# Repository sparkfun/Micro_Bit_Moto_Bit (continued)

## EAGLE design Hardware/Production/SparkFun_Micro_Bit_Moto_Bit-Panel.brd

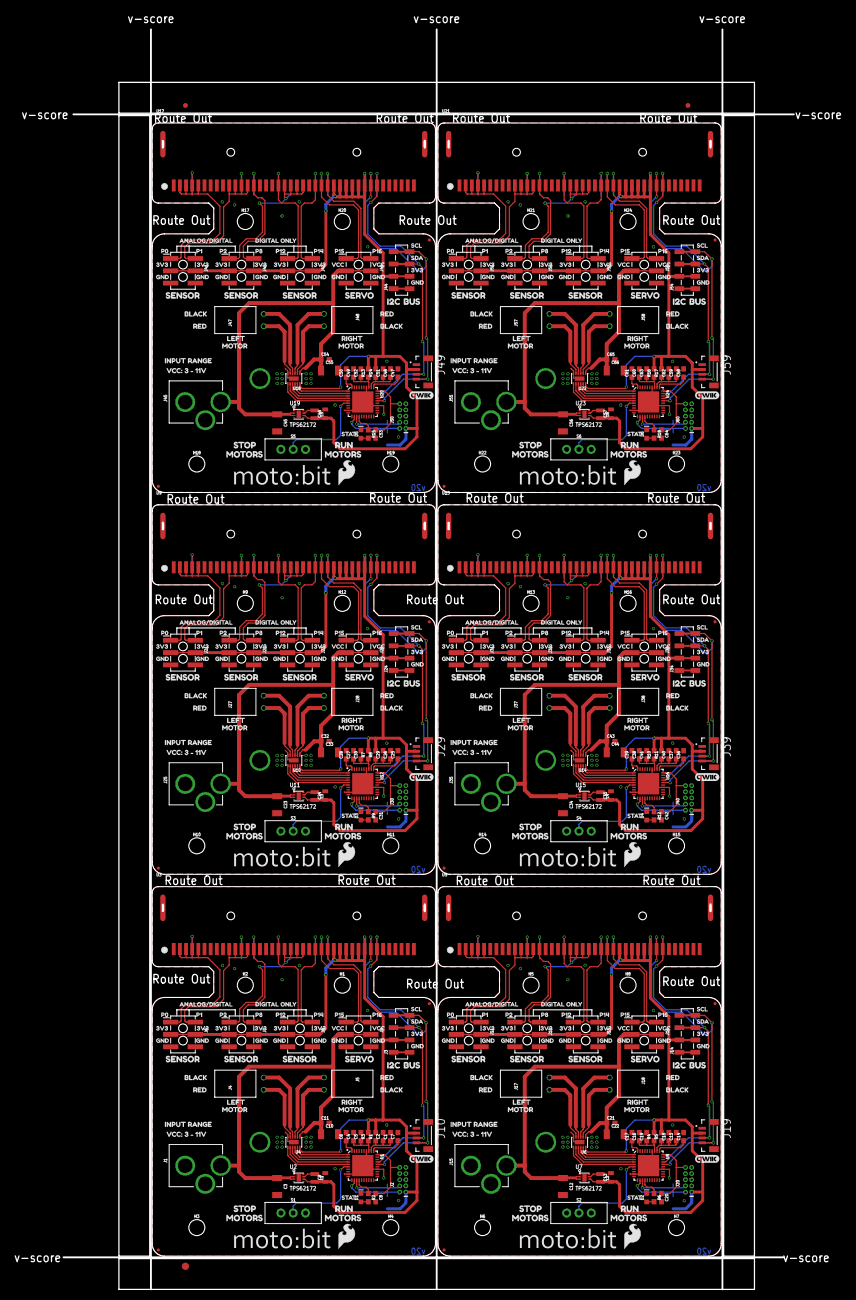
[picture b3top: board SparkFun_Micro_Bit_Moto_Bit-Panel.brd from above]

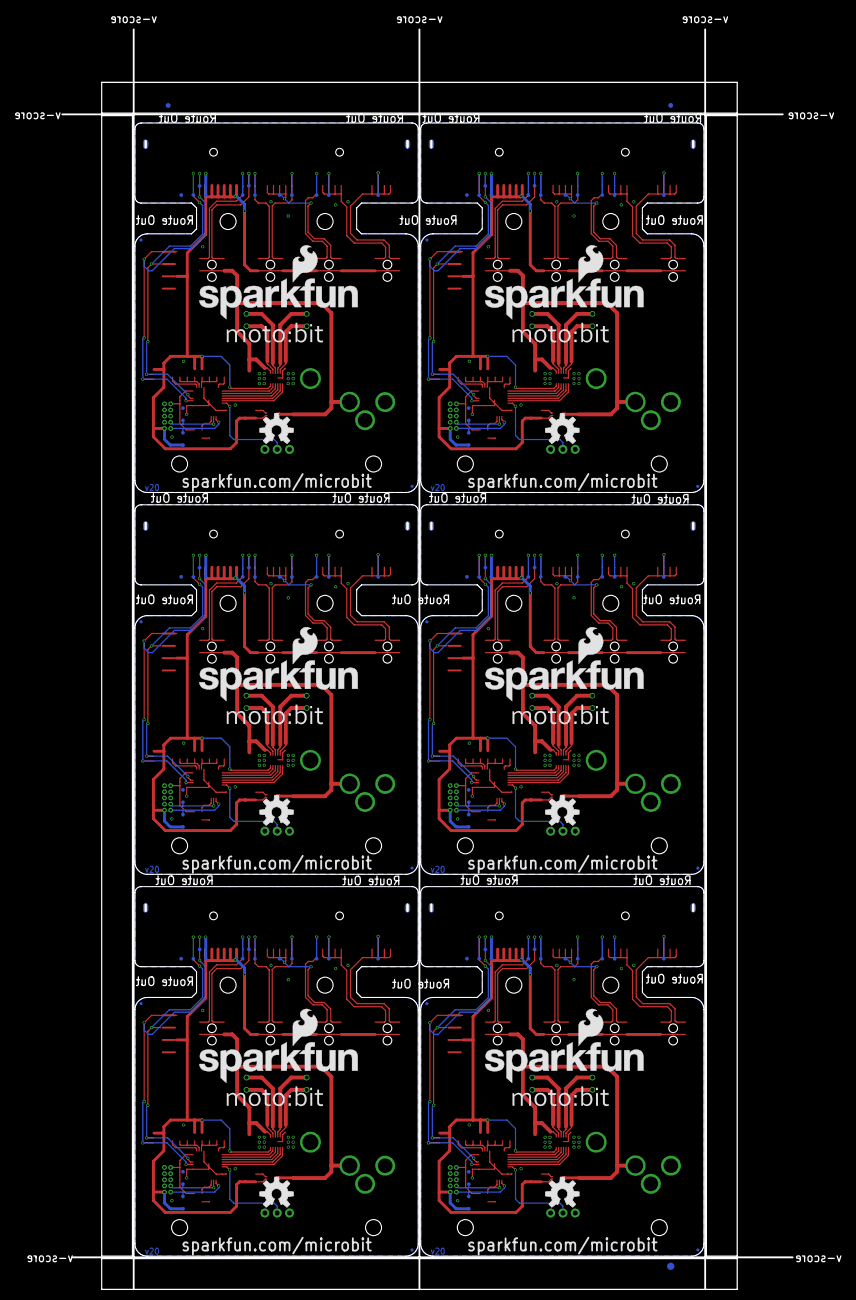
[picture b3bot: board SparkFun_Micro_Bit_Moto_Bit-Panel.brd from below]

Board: 2 copper layers, 172.1 x 263.6 mm, 678 parts (129 on the bottom side), 198 nets.

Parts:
C1, C4, C7, C14, C15, C16, C25, C26, C27, C36, C37, C38, C47, C48, C49, C58, C59, C60: 1.0uF; 0603
C2, C5, C6, C8, C11, C17, C18, C19, C20, C21, C28, C29, C30, C31, C32, C39, C40, C41, C42, C43, C50, C51, C52, C53, C54, C61, C62, C63, C64, C65: 0.1uF; 0603
C3, C10, C12, C22, C23, C33, C34, C44, C45, C55, C56, C66: 10uF; 1210
C9, C13, C24, C35, C46, C57: 22uF; 0805
D1, D2, D3, D4, D5, D6: RED; LED-0603
E$1, E$2, E$3, E$4: FIDUCIAL-1X2
E$5, E$6: FIDUCIAL-1.5X3
FD1, FD2, FD3, FD4, FD5, FD6, FD7, FD8, FD9, FD10, FD11, FD12, FD13, FD14, FD15, FD16, FD17, FD18, FD19, FD20, FD21, FD22, FD23, FD24: FIDUCIALUFIDUCIAL; FIDUCIAL-MICRO
H1, H2, H3, H4, H5, H6, H7, H8, H9, H10, H11, H12, H13, H14, H15, H16, H17, H18, H19, H20, H21, H22, H23, H24: STAND-OFF
J1, J15, J25, J35, J45, J55: POWER_JACKPTH_LOCK; POWER_JACK_PTH_LOCK
J2, J20, J30, J40, J50, J60: CORTEX_JTAG_DEBUG; 2X5-PTH-1.27MM-NO_SILK
J3, J14, J24, J34, J44, J54: 1X04_SMD_VERTICAL_COMBO
J4, J5, J17, J18, J27, J28, J37, J38, J47, J48, J57, J58: 1X02_RA_PTH_FEMALE
J6, J7, J8, J9, J11, J12, J13, J16, J21, J22, J23, J26, J31, J32, J33, J36, J41, J42, J43, J46, J51, J52, J53, J56: 2X3_SMT_POSTS
J10, J19, J29, J39, J49, J59: Qwiic; JST04_1MM_VERT
L1, L2, L3, L4, L5, L6: 2.2μH; 0805-WIDE
LOGO1, LOGO4, LOGO7, LOGO10, LOGO13, LOGO16: SFE_LOGO_NAME_FLAME.3_INCH; SFE_LOGO_NAME_FLAME_.3
LOGO2, LOGO5, LOGO8, LOGO11, LOGO14, LOGO17: OSHW-LOGOL; OSHW-LOGO-L
LOGO3, LOGO6, LOGO9, LOGO12, LOGO15, LOGO18: QWIIC_LOGO_5MM; QWIIC_5MM
R1, R3, R4, R5, R7, R8, R10, R11, R13, R14, R16, R17: 1; 0603
R2, R6, R9, R12, R15, R18: 470; 0603
S1, S2, S3, S4, S5, S6: SWITCH_SPDT_PTH_11.6X4.0MM
TP1, TP2, TP3, TP4, TP5, TP6, TP7, TP8, TP9, TP10, TP11, TP12, TP13, TP14, TP15, TP16, TP17, TP18, TP19, TP20, TP21, TP22, TP23, TP24, TP25, TP26, TP27, TP28, TP29, TP30, TP31, TP32, TP33, TP34, TP35, TP36, TP37, TP38, TP39, TP40, TP41, TP42, TP43, TP44, TP45, TP46, TP47, TP48, TP49, TP50, TP51, TP52, TP53, TP54, TP55, TP56, TP57, TP58, TP59, TP60, TP61, TP62, TP63, TP64, TP65, TP66, TP67, TP68, TP69, TP70, TP71, TP72, TP73, TP74, TP75, TP76, TP77, TP78, TP79, TP80, TP81, TP82, TP83, TP84, TP85, TP86, TP87, TP88, TP89, TP90, TP91, TP92, TP93, TP94, TP95, TP96: PAD.03X.03
U1, U8, U12, U16, U20, U24: CY8C4245LQI-483; QFN-40
U2, U7, U11, U15, U19, U23: TPS62172; WSON-8-PAD
U3, U5, U9, U13, U17, U21: micro:bit; MICRO:BIT-RA_SMD
U4, U6, U10, U14, U18, U22: DRV8835; WSON-12
U$1, U$2, U$109, U$163, U$217, U$271: SFE_LOGO_FLAME_.2
U$3, U$4, U$56, U$57, U$110, U$111, U$164, U$165, U$218, U$219, U$272, U$273: LOGO-MOTOBIT
U$5, U$9, U$12, U$15, U$18, U$21, U$31, U$58, U$62, U$65, U$68, U$71, U$74, U$84, U$112, U$116, U$119, U$122, U$125, U$128, U$138, U$166, U$170, U$173, U$176, U$179, U$182, U$192, U$220, U$224, U$227, U$230, U$233, U$236, U$246, U$274, U$278, U$281, U$284, U$287, U$290, U$300: 3V31
U$6, U$10, U$13, U$16, U$19, U$22, U$25, U$28, U$32, U$59, U$63, U$66, U$69, U$72, U$75, U$78, U$81, U$85, U$113, U$117, U$120, U$123, U$126, U$129, U$132, U$135, U$139, U$167, U$171, U$174, U$177, U$180, U$183, U$186, U$189, U$193, U$221, U$225, U$228, U$231, U$234, U$237, U$240, U$243, U$247, U$275, U$279, U$282, U$285, U$288, U$291, U$294, U$297, U$301: GND0
U$7, U$60, U$114, U$168, U$222, U$276: P02
U$8, U$61, U$115, U$169, U$223, U$277: P13
U$11, U$64, U$118, U$172, U$226, U$280: P24
U$14, U$67, U$121, U$175, U$229, U$283: P85
U$17, U$70, U$124, U$178, U$232, U$286: P126
U$20, U$73, U$127, U$181, U$235, U$289: P147
U$23, U$76, U$130, U$184, U$238, U$292: P158
U$24, U$27, U$77, U$80, U$131, U$134, U$185, U$188, U$239, U$242, U$293, U$296: VCC10
U$26, U$79, U$133, U$187, U$241, U$295: P169
U$29, U$82, U$136, U$190, U$244, U$298: SCL2
U$30, U$83, U$137, U$191, U$245, U$299: SDA3
U$33, U$86, U$140, U$194, U$248, U$302: I2C4
U$34, U$87, U$141, U$195, U$249, U$303: BUS5
U$35, U$88, U$142, U$196, U$250, U$304: SERVO6
U$36, U$37, U$38, U$89, U$90, U$91, U$143, U$144, U$145, U$197, U$198, U$199, U$251, U$252, U$253, U$305, U$306, U$307: SENSOR7
U$39, U$92, U$146, U$200, U$254, U$308: ANALOG#DIGITAL0
U$40, U$93, U$147, U$201, U$255, U$309: DIGITAL_ONLY1
U$41, U$44, U$94, U$97, U$148, U$151, U$202, U$205, U$256, U$259, U$310, U$313: BLACK8
U$42, U$43, U$95, U$96, U$149, U$150, U$203, U$204, U$257, U$258, U$311, U$312: RED9
U$45, U$98, U$152, U$206, U$260, U$314: LEFT10
U$46, U$48, U$99, U$101, U$153, U$155, U$207, U$209, U$261, U$263, U$315, U$317: MOTOR11
U$47, U$100, U$154, U$208, U$262, U$316: RIGHT12
U$49, U$102, U$156, U$210, U$264, U$318: INPUT_RANGE13
U$50, U$103, U$157, U$211, U$265, U$319: VCC#_3_#_11V14
U$51, U$104, U$158, U$212, U$266, U$320: STOP15
U$52, U$54, U$105, U$107, U$159, U$161, U$213, U$215, U$267, U$269, U$321, U$323: MOTORS16
U$53, U$106, U$160, U$214, U$268, U$322: RUN17
U$55, U$108, U$162, U$216, U$270, U$324: STAT18

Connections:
3.3V: C9.1, J2.1, J3.2, J6.3, J6.4, J7.3, J7.4, J8.3, J8.4, J10.2, L1.2, R1.2, R3.2, TP1.P$1, TP15.P$1, U2.6, U3.P$27, U3.P$28, U3.P$29, U3.P$30, U3.P$31, U3.P$32, U4.12
3.3V1: C13.1, J11.3, J11.4, J12.3, J12.4, J13.3, J13.4, J14.2, J19.2, J20.1, L2.2, R4.2, R5.2, TP19.P$1, TP31.P$1, U5.P$27, U5.P$28, U5.P$29, U5.P$30, U5.P$31, U5.P$32, U6.12, U7.6
3.3V2: C24.1, J21.3, J21.4, J22.3, J22.4, J23.3, J23.4, J24.2, J29.2, J30.1, L3.2, R7.2, R8.2, TP35.P$1, TP47.P$1, U9.P$27, U9.P$28, U9.P$29, U9.P$30, U9.P$31, U9.P$32, U10.12, U11.6
3.3V3: C35.1, J31.3, J31.4, J32.3, J32.4, J33.3, J33.4, J34.2, J39.2, J40.1, L4.2, R10.2, R11.2, TP51.P$1, TP63.P$1, U13.P$27, U13.P$28, U13.P$29, U13.P$30, U13.P$31, U13.P$32, U14.12, U15.6
3.3V4: C46.1, J41.3, J41.4, J42.3, J42.4, J43.3, J43.4, J44.2, J49.2, J50.1, L5.2, R13.2, R14.2, TP67.P$1, TP79.P$1, U17.P$27, U17.P$28, U17.P$29, U17.P$30, U17.P$31, U17.P$32, U18.12, U19.6
3.3V5: C57.1, J51.3, J51.4, J52.3, J52.4, J53.3, J53.4, J54.2, J59.2, J60.1, L6.2, R16.2, R17.2, TP83.P$1, TP95.P$1, U21.P$27, U21.P$28, U21.P$29, U21.P$30, U21.P$31, U21.P$32, U22.12, U23.6
!RESET: C8.1, J2.10, U1.30
!RESET1: C20.1, J20.10, U8.30
!RESET2: C31.1, J30.10, U12.30
!RESET3: C42.1, J40.10, U16.30
!RESET4: C53.1, J50.10, U20.30
!RESET5: C64.1, J60.10, U24.30
ANALOG_0: J6.1, TP5.P$1, U3.P$2, U3.P$3, U3.P$4, U3.P$5
ANALOG_1: J6.2, TP6.P$1, U3.P$10, U3.P$11, U3.P$12, U3.P$13
ANALOG_2: J7.1, TP8.P$1, U3.P$19, U3.P$20, U3.P$21, U3.P$22
ANALOG_3: J12.1, TP24.P$1, U5.P$19, U5.P$20, U5.P$21, U5.P$22
ANALOG_4: J11.2, TP22.P$1, U5.P$10, U5.P$11, U5.P$12, U5.P$13
ANALOG_5: J11.1, TP21.P$1, U5.P$2, U5.P$3, U5.P$4, U5.P$5
ANALOG_6: J22.1, TP40.P$1, U9.P$19, U9.P$20, U9.P$21, U9.P$22
ANALOG_7: J21.2, TP38.P$1, U9.P$10, U9.P$11, U9.P$12, U9.P$13
ANALOG_8: J21.1, TP37.P$1, U9.P$2, U9.P$3, U9.P$4, U9.P$5
ANALOG_9: J32.1, TP56.P$1, U13.P$19, U13.P$20, U13.P$21, U13.P$22
ANALOG_10: J31.2, TP54.P$1, U13.P$10, U13.P$11, U13.P$12, U13.P$13
ANALOG_11: J31.1, TP53.P$1, U13.P$2, U13.P$3, U13.P$4, U13.P$5
ANALOG_12: J42.1, TP72.P$1, U17.P$19, U17.P$20, U17.P$21, U17.P$22
ANALOG_13: J41.2, TP70.P$1, U17.P$10, U17.P$11, U17.P$12, U17.P$13
ANALOG_14: J41.1, TP69.P$1, U17.P$2, U17.P$3, U17.P$4, U17.P$5
ANALOG_15: J52.1, TP88.P$1, U21.P$19, U21.P$20, U21.P$21, U21.P$22
ANALOG_16: J51.2, TP86.P$1, U21.P$10, U21.P$11, U21.P$12, U21.P$13
ANALOG_17: J51.1, TP85.P$1, U21.P$2, U21.P$3, U21.P$4, U21.P$5
AO1: J5.1, U4.2
AO2: J5.2, U4.3
AO3: J18.1, U6.2
AO4: J18.2, U6.3
AO5: J28.1, U10.2
AO6: J28.2, U10.3
AO7: J38.1, U14.2
AO8: J38.2, U14.3
AO9: J48.1, U18.2
AO10: J48.2, U18.3
AO11: J58.1, U22.2
AO12: J58.2, U22.3
BO1: J4.1, U4.4
BO2: J4.2, U4.5
BO3: J17.1, U6.4
BO4: J17.2, U6.5
BO5: J27.1, U10.4
BO6: J27.2, U10.5
BO7: J37.1, U14.4
BO8: J37.2, U14.5
BO9: J47.1, U18.4
BO10: J47.2, U18.5
BO11: J57.1, U22.4
BO12: J57.2, U22.5
DIGITAL_1: J12.2, TP23.P$1, U5.P$14
DIGITAL_2: J13.1, TP25.P$1, U5.P$18
DIGITAL_3: J13.2, TP26.P$1, U5.P$24
DIGITAL_4: J22.2, TP39.P$1, U9.P$14
DIGITAL_5: J23.1, TP41.P$1, U9.P$18
DIGITAL_6: J23.2, TP42.P$1, U9.P$24
DIGITAL_7: J32.2, TP55.P$1, U13.P$14
DIGITAL_8: J7.2, TP7.P$1, U3.P$14
DIGITAL_9: J33.1, TP57.P$1, U13.P$18
DIGITAL_10: J33.2, TP58.P$1, U13.P$24
DIGITAL_11: J42.2, TP71.P$1, U17.P$14
DIGITAL_12: J8.1, TP9.P$1, U3.P$18
DIGITAL_13: J43.1, TP73.P$1, U17.P$18
DIGITAL_14: J8.2, TP10.P$1, U3.P$24
DIGITAL_15: J43.2, TP74.P$1, U17.P$24
DIGITAL_16: J52.2, TP87.P$1, U21.P$14
DIGITAL_17: J53.1, TP89.P$1, U21.P$18
DIGITAL_18: J53.2, TP90.P$1, U21.P$24
GND: C1.2, C2.2, C3.2, C4.2, C5.2, C6.2, C7.2, C8.2, C9.2, C10.2, C11.2, D1.C, J1.GND, J1.GNDBREAK, J2.3, J2.5, J2.9, J3.1, J6.5, J6.6, J7.5, J7.6, J8.5, J8.6, J9.5, J9.6, J10.1, S1.3, TP2.P$1, TP16.P$1, U1.9, U1.24, U1.34, U1.EP, U2.1, U2.4, U2.5, U2.PAD, U3.P$35, U3.P$36, U3.P$37, U3.P$38, U3.P$39, U3.P$40, U4.6, U4.PAD
GND1: C12.2, C13.2, C14.2, C15.2, C16.2, C17.2, C18.2, C19.2, C20.2, C21.2, C22.2, D2.C, J11.5, J11.6, J12.5, J12.6, J13.5, J13.6, J14.1, J15.GND, J15.GNDBREAK, J16.5, J16.6, J19.1, J20.3, J20.5, J20.9, S2.3, TP20.P$1, TP32.P$1, U5.P$35, U5.P$36, U5.P$37, U5.P$38, U5.P$39, U5.P$40, U6.6, U6.PAD, U7.1, U7.4, U7.5, U7.PAD, U8.9, U8.24, U8.34, U8.EP
GND2: C23.2, C24.2, C25.2, C26.2, C27.2, C28.2, C29.2, C30.2, C31.2, C32.2, C33.2, D3.C, J21.5, J21.6, J22.5, J22.6, J23.5, J23.6, J24.1, J25.GND, J25.GNDBREAK, J26.5, J26.6, J29.1, J30.3, J30.5, J30.9, S3.3, TP36.P$1, TP48.P$1, U9.P$35, U9.P$36, U9.P$37, U9.P$38, U9.P$39, U9.P$40, U10.6, U10.PAD, U11.1, U11.4, U11.5, U11.PAD, U12.9, U12.24, U12.34, U12.EP
GND3: C34.2, C35.2, C36.2, C37.2, C38.2, C39.2, C40.2, C41.2, C42.2, C43.2, C44.2, D4.C, J31.5, J31.6, J32.5, J32.6, J33.5, J33.6, J34.1, J35.GND, J35.GNDBREAK, J36.5, J36.6, J39.1, J40.3, J40.5, J40.9, S4.3, TP52.P$1, TP64.P$1, U13.P$35, U13.P$36, U13.P$37, U13.P$38, U13.P$39, U13.P$40, U14.6, U14.PAD, U15.1, U15.4, U15.5, U15.PAD, U16.9, U16.24, U16.34, U16.EP
GND4: C45.2, C46.2, C47.2, C48.2, C49.2, C50.2, C51.2, C52.2, C53.2, C54.2, C55.2, D5.C, J41.5, J41.6, J42.5, J42.6, J43.5, J43.6, J44.1, J45.GND, J45.GNDBREAK, J46.5, J46.6, J49.1, J50.3, J50.5, J50.9, S5.3, TP68.P$1, TP80.P$1, U17.P$35, U17.P$36, U17.P$37, U17.P$38, U17.P$39, U17.P$40, U18.6, U18.PAD, U19.1, U19.4, U19.5, U19.PAD, U20.9, U20.24, U20.34, U20.EP
GND5: C56.2, C57.2, C58.2, C59.2, C60.2, C61.2, C62.2, C63.2, C64.2, C65.2, C66.2, D6.C, J51.5, J51.6, J52.5, J52.6, J53.5, J53.6, J54.1, J55.GND, J55.GNDBREAK, J56.5, J56.6, J59.1, J60.3, J60.5, J60.9, S6.3, TP84.P$1, TP96.P$1, U21.P$35, U21.P$36, U21.P$37, U21.P$38, U21.P$39, U21.P$40, U22.6, U22.PAD, U23.1, U23.4, U23.5, U23.PAD, U24.9, U24.24, U24.34, U24.EP
unnamed: C7.1, U1.31
unnamed: C6.1, U1.40
unnamed: C4.1, C5.1, R3.1, U1.33
unnamed: L1.1, U2.7
unnamed: C14.1, U8.31
unnamed: C16.1, C19.1, R4.1, U8.33
unnamed: C17.1, U8.40
unnamed: D1.A, R2.2
unnamed: D2.A, R6.2
unnamed: L2.1, U7.7
unnamed: C25.1, U12.31
unnamed: C27.1, C30.1, R7.1, U12.33
unnamed: C28.1, U12.40
unnamed: D3.A, R9.2
unnamed: L3.1, U11.7
unnamed: C36.1, U16.31
unnamed: C38.1, C41.1, R10.1, U16.33
unnamed: C39.1, U16.40
unnamed: D4.A, R12.2
unnamed: L4.1, U15.7
unnamed: C47.1, U20.31
unnamed: C49.1, C52.1, R13.1, U20.33
unnamed: C50.1, U20.40
unnamed: D5.A, R15.2
unnamed: L5.1, U19.7
unnamed: C58.1, U24.31
unnamed: C60.1, C63.1, R16.1, U24.33
unnamed: C61.1, U24.40
unnamed: D6.A, R18.2
unnamed: L6.1, U23.7
P2.0: U1.1, U4.11
P2.1: U1.2, U4.10
P2.2: U1.3, U4.9
P2.3: U1.4, U4.8
P2.4: U1.5, U4.7
P2.5: U6.10, U8.2
P2.6: U6.9, U8.3
P2.7: U6.8, U8.4
P2.8: U6.7, U8.5
P2.9: U6.11, U8.1
P2.10: U10.10, U12.2
P2.11: U10.9, U12.3
P2.12: U10.8, U12.4
P2.13: U10.7, U12.5
P2.14: U10.11, U12.1
P2.15: U14.10, U16.2
P2.16: U14.9, U16.3
P2.17: U14.8, U16.4
P2.18: U14.7, U16.5
P2.19: U14.11, U16.1
P2.20: U18.10, U20.2
P2.21: U18.9, U20.3
P2.22: U18.8, U20.4
P2.23: U18.7, U20.5
P2.24: U18.11, U20.1
P2.25: U22.10, U24.2
P2.26: U22.9, U24.3
P2.27: U22.8, U24.4
P2.28: U22.7, U24.5
P2.29: U22.11, U24.1
P3.1: J20.2, TP17.P$1, U8.12
P3.2: J2.2, TP3.P$1, U1.12
P3.3: J2.4, TP4.P$1, U1.13
P3.4: J20.4, TP18.P$1, U8.13
P3.5: J30.2, TP33.P$1, U12.12
P3.6: J30.4, TP34.P$1, U12.13
P3.7: J40.2, TP49.P$1, U16.12
P3.8: J40.4, TP50.P$1, U16.13
P3.9: J50.2, TP65.P$1, U20.12
P3.10: J50.4, TP66.P$1, U20.13
P3.11: J60.2, TP81.P$1, U24.12
P3.12: J60.4, TP82.P$1, U24.13
SCL: J3.4, J10.4, TP13.P$1, U1.26, U3.P$33
SCL1: J14.4, J19.4, TP29.P$1, U5.P$33, U8.26
SCL2: J24.4, J29.4, TP45.P$1, U9.P$33, U12.26
SCL3: J34.4, J39.4, TP61.P$1, U13.P$33, U16.26
SCL4: J44.4, J49.4, TP77.P$1, U17.P$33, U20.26
SCL5: J54.4, J59.4, TP93.P$1, U21.P$33, U24.26
SDA: J3.3, J10.3, TP14.P$1, U1.27, U3.P$34
SDA1: J14.3, J19.3, TP30.P$1, U5.P$34, U8.27
SDA2: J24.3, J29.3, TP46.P$1, U9.P$34, U12.27
SDA3: J34.3, J39.3, TP62.P$1, U13.P$34, U16.27
SDA4: J44.3, J49.3, TP78.P$1, U17.P$34, U20.27
SDA5: J54.3, J59.3, TP94.P$1, U21.P$34, U24.27
SERVO_1: J16.2, TP28.P$1, U5.P$26
SERVO_2: J16.1, TP27.P$1, U5.P$25
SERVO_3: J26.2, TP44.P$1, U9.P$26
SERVO_4: J26.1, TP43.P$1, U9.P$25
SERVO_5: J36.2, TP60.P$1, U13.P$26
SERVO_6: J36.1, TP59.P$1, U13.P$25
SERVO_7: J46.2, TP76.P$1, U17.P$26
SERVO_8: J46.1, TP75.P$1, U17.P$25
SERVO_9: J56.2, TP92.P$1, U21.P$26
SERVO_10: J56.1, TP91.P$1, U21.P$25
SERVO_15: J9.1, TP11.P$1, U3.P$25
SERVO_16: J9.2, TP12.P$1, U3.P$26
SLED: R2.1, U1.14
SLED1: R6.1, U8.14
SLED2: R9.1, U12.14
SLED3: R12.1, U16.14
SLED4: R15.1, U20.14
SLED5: R18.1, U24.14
U2.1: S2.2, U8.6
U2.2: S3.2, U12.6
U2.3: S4.2, U16.6
U2.4: S5.2, U20.6
U2.5: S1.2, U1.6
U2.6: S6.2, U24.6
VCC: C3.1, C10.1, C11.1, J1.PWR, J9.3, J9.4, U2.2, U2.3, U4.1
VCC1: C12.1, C21.1, C22.1, J15.PWR, J16.3, J16.4, U6.1, U7.2, U7.3
VCC2: C23.1, C32.1, C33.1, J25.PWR, J26.3, J26.4, U10.1, U11.2, U11.3
VCC3: C34.1, C43.1, C44.1, J35.PWR, J36.3, J36.4, U14.1, U15.2, U15.3
VCC4: C45.1, C54.1, C55.1, J45.PWR, J46.3, J46.4, U18.1, U19.2, U19.3
VCC5: C56.1, C65.1, C66.1, J55.PWR, J56.3, J56.4, U22.1, U23.2, U23.3
VDDD: C1.1, C2.1, R1.1, U1.32
VDDD1: C15.1, C18.1, R5.1, U8.32
VDDD2: C26.1, C29.1, R8.1, U12.32
VDDD3: C37.1, C40.1, R11.1, U16.32
VDDD4: C48.1, C51.1, R14.1, U20.32
VDDD5: C59.1, C62.1, R17.1, U24.32

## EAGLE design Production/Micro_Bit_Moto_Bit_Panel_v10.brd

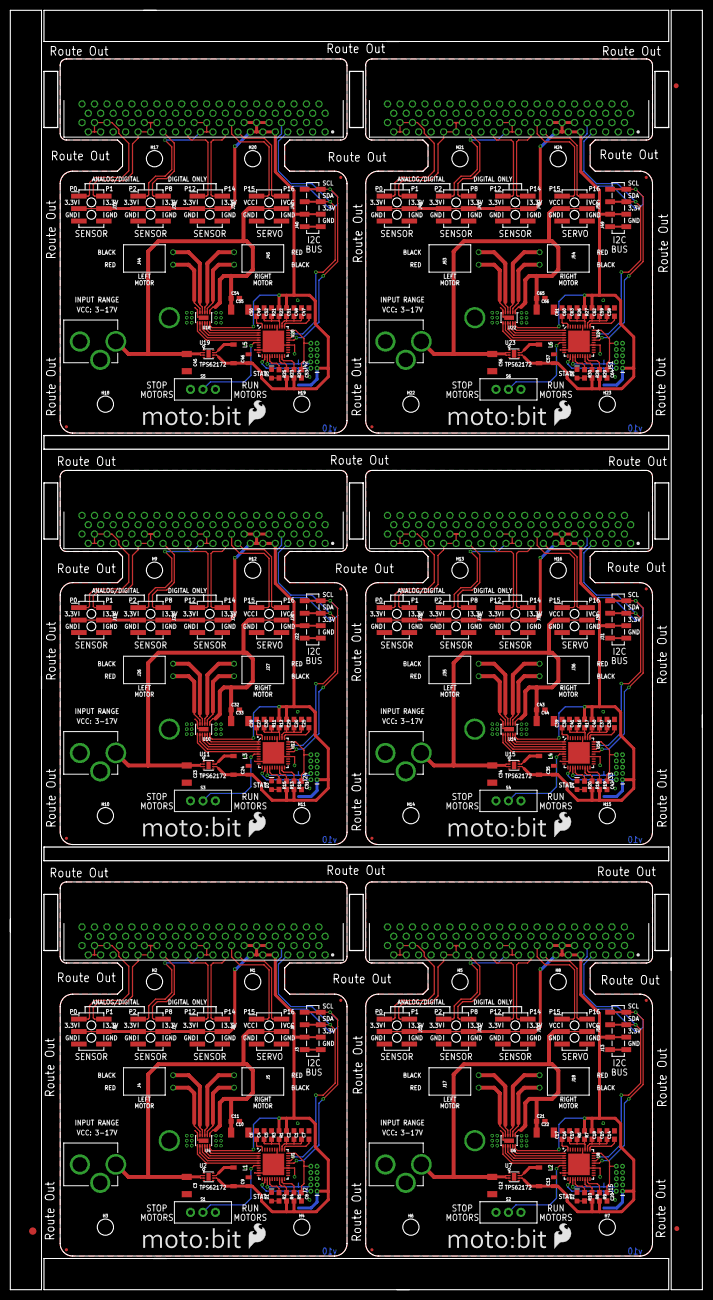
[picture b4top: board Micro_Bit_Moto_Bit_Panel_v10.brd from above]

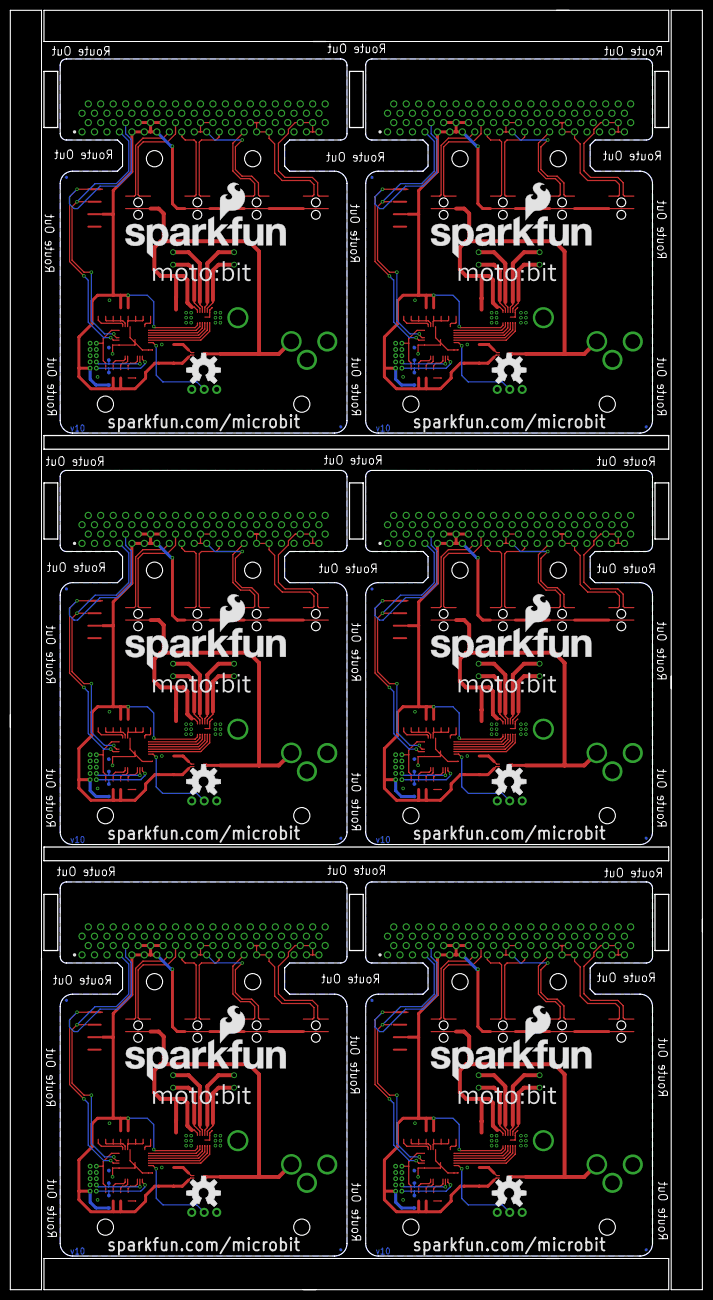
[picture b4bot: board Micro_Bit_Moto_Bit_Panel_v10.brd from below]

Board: 2 copper layers, 140.9 x 260.6 mm, 297 parts (54 on the bottom side), 210 nets.

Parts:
C1, C4, C7, C14, C15, C16, C25, C26, C27, C36, C37, C38, C47, C48, C49, C58, C59, C60: 1.0uF; 0603
C2, C5, C6, C8, C11, C17, C18, C19, C20, C21, C28, C29, C30, C31, C32, C39, C40, C41, C42, C43, C50, C51, C52, C53, C54, C61, C62, C63, C64, C65: 0.1uF; 0603
C3, C10, C12, C22, C23, C33, C34, C44, C45, C55, C56, C66: 10uF; 1210
C9, C13, C24, C35, C46, C57: 22uF; 0805
D1, D2, D3, D4, D5, D6: RED; LED-0603
E$1: FIDUCIAL-1.5X3
E$5, E$7: FIDUCIAL-1X2
FD1, FD2, FD3, FD4, FD5, FD6, FD7, FD8, FD9, FD10, FD11, FD12, FD13, FD14, FD15, FD16, FD17, FD18, FD19, FD20, FD21, FD22, FD23, FD24: FIDUCIALUFIDUCIAL; FIDUCIAL-MICRO
H1, H2, H3, H4, H5, H6, H7, H8, H9, H10, H11, H12, H13, H14, H15, H16, H17, H18, H19, H20, H21, H22, H23, H24: STAND-OFF
J1, J14, J23, J32, J41, J50: POWER_JACKPTH_LOCK; POWER_JACK_PTH_LOCK
J2, J15, J24, J33, J42, J51: CORTEX_DEBUGPTH; 2X5-PTH-1.27MM
J3, J13, J22, J31, J40, J49: 1X04_SMD_VERTICAL_COMBO
J4, J5, J17, J18, J26, J27, J35, J36, J44, J45, J53, J54: 1X02_RA_FEMALE
J6, J7, J8, J9, J10, J11, J12, J16, J19, J20, J21, J25, J28, J29, J30, J34, J37, J38, J39, J43, J46, J47, J48, J52: 2X3_SMT_POSTS
L1, L2, L3, L4, L5, L6: 2.2µH; INDUCTOR_2.2UH
LOGO1, LOGO3, LOGO5, LOGO7, LOGO9, LOGO11: SFE_LOGO_NAME_FLAME.3_INCH; SFE_LOGO_NAME_FLAME_.3
LOGO2, LOGO4, LOGO6, LOGO8, LOGO10, LOGO12: OSHW-LOGOL; OSHW-LOGO-L
R1, R3, R6, R7, R11, R12, R16, R17, R21, R22, R26, R27: 1; 0603
R2, R10, R15, R20, R25, R30: 470; 0603
R4, R5, R8, R9, R13, R14, R18, R19, R23, R24, R28, R29: 4.7k; 0603
S1, S2, S3, S4, S5, S6: SWITCH_SPDT_PTH_11.6X4.0MM
TP1, TP2, TP3, TP4, TP5, TP6, TP7, TP8, TP9, TP10, TP11, TP12, TP13, TP14, TP15, TP16, TP17, TP18, TP19, TP20, TP21, TP22, TP23, TP24: PAD.03X.03
U1, U8, U12, U16, U20, U24: CY8C4245LQI-483; QFN-40
U2, U7, U11, U15, U19, U23: TPS62172; WSON-8-PAD
U3, U5, U9, U13, U17, U21: micro:bit; MICRO:BIT_RA_PTH
U4, U6, U10, U14, U18, U22: DRV8835; WSON-12
U$2, U$5, U$8, U$11, U$14, U$17: SFE_LOGO_FLAME_.2
U$3, U$4, U$6, U$7, U$9, U$10, U$12, U$13, U$15, U$16, U$18, U$19: LOGO-MOTOBIT

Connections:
3.3V: C9.1, J2.1, J3.2, J6.3, J6.4, J7.3, J7.4, J8.3, J8.4, L1.P$2, R1.2, R3.2, R4.2, R5.2, TP3.P$1, U2.6, U3.A9, U3.A10, U3.A11, U3.A12, U3.A13, U3.A14, U4.12
3.3V1: C13.1, J10.3, J10.4, J11.3, J11.4, J12.3, J12.4, J13.2, J15.1, L2.P$2, R6.2, R7.2, R8.2, R9.2, TP7.P$1, U5.A9, U5.A10, U5.A11, U5.A12, U5.A13, U5.A14, U6.12, U7.6
3.3V2: C24.1, J19.3, J19.4, J20.3, J20.4, J21.3, J21.4, J22.2, J24.1, L3.P$2, R11.2, R12.2, R13.2, R14.2, TP11.P$1, U9.A9, U9.A10, U9.A11, U9.A12, U9.A13, U9.A14, U10.12, U11.6
3.3V3: C35.1, J28.3, J28.4, J29.3, J29.4, J30.3, J30.4, J31.2, J33.1, L4.P$2, R16.2, R17.2, R18.2, R19.2, TP15.P$1, U13.A9, U13.A10, U13.A11, U13.A12, U13.A13, U13.A14, U14.12, U15.6
3.3V4: C46.1, J37.3, J37.4, J38.3, J38.4, J39.3, J39.4, J40.2, J42.1, L5.P$2, R21.2, R22.2, R23.2, R24.2, TP19.P$1, U17.A9, U17.A10, U17.A11, U17.A12, U17.A13, U17.A14, U18.12, U19.6
3.3V5: C57.1, J46.3, J46.4, J47.3, J47.4, J48.3, J48.4, J49.2, J51.1, L6.P$2, R26.2, R27.2, R28.2, R29.2, TP23.P$1, U21.A9, U21.A10, U21.A11, U21.A12, U21.A13, U21.A14, U22.12, U23.6
!RESET: C8.1, J2.10, U1.30
!RESET1: C20.1, J15.10, U8.30
!RESET2: C31.1, J24.10, U12.30
!RESET3: C42.1, J33.10, U16.30
!RESET4: C53.1, J42.10, U20.30
!RESET5: C64.1, J51.10, U24.30
ANALOG_0: J6.1, U3.A36, U3.A37, U3.A38, U3.A39
ANALOG_1: J6.2, U3.A28, U3.A29, U3.A30, U3.A31
ANALOG_2: J7.1, U3.A19, U3.A20, U3.A21, U3.A22
ANALOG_3: J11.1, U5.A19, U5.A20, U5.A21, U5.A22
ANALOG_4: J10.2, U5.A28, U5.A29, U5.A30, U5.A31
ANALOG_5: J10.1, U5.A36, U5.A37, U5.A38, U5.A39
ANALOG_6: J20.1, U9.A19, U9.A20, U9.A21, U9.A22
ANALOG_7: J19.2, U9.A28, U9.A29, U9.A30, U9.A31
ANALOG_8: J19.1, U9.A36, U9.A37, U9.A38, U9.A39
ANALOG_9: J29.1, U13.A19, U13.A20, U13.A21, U13.A22
ANALOG_10: J28.2, U13.A28, U13.A29, U13.A30, U13.A31
ANALOG_11: J28.1, U13.A36, U13.A37, U13.A38, U13.A39
ANALOG_12: J38.1, U17.A19, U17.A20, U17.A21, U17.A22
ANALOG_13: J37.2, U17.A28, U17.A29, U17.A30, U17.A31
ANALOG_14: J37.1, U17.A36, U17.A37, U17.A38, U17.A39
ANALOG_15: J47.1, U21.A19, U21.A20, U21.A21, U21.A22
ANALOG_16: J46.2, U21.A28, U21.A29, U21.A30, U21.A31
ANALOG_17: J46.1, U21.A36, U21.A37, U21.A38, U21.A39
AO1: J5.1, U4.2
AO2: J5.2, U4.3
AO3: J18.1, U6.2
AO4: J18.2, U6.3
AO5: J27.1, U10.2
AO6: J27.2, U10.3
AO7: J36.1, U14.2
AO8: J36.2, U14.3
AO9: J45.1, U18.2
AO10: J45.2, U18.3
AO11: J54.1, U22.2
AO12: J54.2, U22.3
BO1: J4.1, U4.4
BO2: J4.2, U4.5
BO3: J17.1, U6.4
BO4: J17.2, U6.5
BO5: J26.1, U10.4
BO6: J26.2, U10.5
BO7: J35.1, U14.4
BO8: J35.2, U14.5
BO9: J44.1, U18.4
BO10: J44.2, U18.5
BO11: J53.1, U22.4
BO12: J53.2, U22.5
DIGITAL_1: J11.2, U5.A27
DIGITAL_2: J12.1, U5.A23
DIGITAL_3: J12.2, U5.A17
DIGITAL_4: J20.2, U9.A27
DIGITAL_5: J21.1, U9.A23
DIGITAL_6: J21.2, U9.A17
DIGITAL_7: J29.2, U13.A27
DIGITAL_8: J7.2, U3.A27
DIGITAL_9: J30.1, U13.A23
DIGITAL_10: J30.2, U13.A17
DIGITAL_11: J38.2, U17.A27
DIGITAL_12: J8.1, U3.A23
DIGITAL_13: J39.1, U17.A23
DIGITAL_14: J8.2, U3.A17
DIGITAL_15: J39.2, U17.A17
DIGITAL_16: J47.2, U21.A27
DIGITAL_17: J48.1, U21.A23
DIGITAL_18: J48.2, U21.A17
GND: C1.2, C2.2, C3.2, C4.2, C5.2, C6.2, C7.2, C8.2, C9.2, C10.2, C11.2, D1.C, J1.GND, J1.GNDBREAK, J2.3, J2.5, J2.7, J2.9, J3.1, J6.5, J6.6, J7.5, J7.6, J8.5, J8.6, J9.5, J9.6, S1.3, TP4.P$1, U1.9, U1.24, U1.34, U1.EP, U2.1, U2.4, U2.5, U2.PAD, U3.A1, U3.A2, U3.A3, U3.A4, U3.A5, U3.A6, U4.6, U4.PAD
GND1: C12.2, C13.2, C14.2, C15.2, C16.2, C17.2, C18.2, C19.2, C20.2, C21.2, C22.2, D2.C, J10.5, J10.6, J11.5, J11.6, J12.5, J12.6, J13.1, J14.GND, J14.GNDBREAK, J15.3, J15.5, J15.7, J15.9, J16.5, J16.6, S2.3, TP8.P$1, U5.A1, U5.A2, U5.A3, U5.A4, U5.A5, U5.A6, U6.6, U6.PAD, U7.1, U7.4, U7.5, U7.PAD, U8.9, U8.24, U8.34, U8.EP
GND2: C23.2, C24.2, C25.2, C26.2, C27.2, C28.2, C29.2, C30.2, C31.2, C32.2, C33.2, D3.C, J19.5, J19.6, J20.5, J20.6, J21.5, J21.6, J22.1, J23.GND, J23.GNDBREAK, J24.3, J24.5, J24.7, J24.9, J25.5, J25.6, S3.3, TP12.P$1, U9.A1, U9.A2, U9.A3, U9.A4, U9.A5, U9.A6, U10.6, U10.PAD, U11.1, U11.4, U11.5, U11.PAD, U12.9, U12.24, U12.34, U12.EP
GND3: C34.2, C35.2, C36.2, C37.2, C38.2, C39.2, C40.2, C41.2, C42.2, C43.2, C44.2, D4.C, J28.5, J28.6, J29.5, J29.6, J30.5, J30.6, J31.1, J32.GND, J32.GNDBREAK, J33.3, J33.5, J33.7, J33.9, J34.5, J34.6, S4.3, TP16.P$1, U13.A1, U13.A2, U13.A3, U13.A4, U13.A5, U13.A6, U14.6, U14.PAD, U15.1, U15.4, U15.5, U15.PAD, U16.9, U16.24, U16.34, U16.EP
GND4: C45.2, C46.2, C47.2, C48.2, C49.2, C50.2, C51.2, C52.2, C53.2, C54.2, C55.2, D5.C, J37.5, J37.6, J38.5, J38.6, J39.5, J39.6, J40.1, J41.GND, J41.GNDBREAK, J42.3, J42.5, J42.7, J42.9, J43.5, J43.6, S5.3, TP20.P$1, U17.A1, U17.A2, U17.A3, U17.A4, U17.A5, U17.A6, U18.6, U18.PAD, U19.1, U19.4, U19.5, U19.PAD, U20.9, U20.24, U20.34, U20.EP
GND5: C56.2, C57.2, C58.2, C59.2, C60.2, C61.2, C62.2, C63.2, C64.2, C65.2, C66.2, D6.C, J46.5, J46.6, J47.5, J47.6, J48.5, J48.6, J49.1, J50.GND, J50.GNDBREAK, J51.3, J51.5, J51.7, J51.9, J52.5, J52.6, S6.3, TP24.P$1, U21.A1, U21.A2, U21.A3, U21.A4, U21.A5, U21.A6, U22.6, U22.PAD, U23.1, U23.4, U23.5, U23.PAD, U24.9, U24.24, U24.34, U24.EP
unnamed: C7.1, U1.31
unnamed: C6.1, U1.40
unnamed: C4.1, C5.1, R3.1, U1.33
unnamed: L1.P$1, U2.7
unnamed: L2.P$1, U7.7
unnamed: R4.1, U1.18
unnamed: R5.1, U1.19
unnamed: D1.A, R2.2
unnamed: C14.1, U8.31
unnamed: C16.1, C19.1, R6.1, U8.33
unnamed: C17.1, U8.40
unnamed: R8.1, U8.18
unnamed: R9.1, U8.19
unnamed: D2.A, R10.2
unnamed: L3.P$1, U11.7
unnamed: C25.1, U12.31
unnamed: C27.1, C30.1, R11.1, U12.33
unnamed: C28.1, U12.40
unnamed: R13.1, U12.18
unnamed: R14.1, U12.19
unnamed: D3.A, R15.2
unnamed: L4.P$1, U15.7
unnamed: C36.1, U16.31
unnamed: C38.1, C41.1, R16.1, U16.33
unnamed: C39.1, U16.40
unnamed: R18.1, U16.18
unnamed: R19.1, U16.19
unnamed: D4.A, R20.2
unnamed: L5.P$1, U19.7
unnamed: C47.1, U20.31
unnamed: C49.1, C52.1, R21.1, U20.33
unnamed: C50.1, U20.40
unnamed: R23.1, U20.18
unnamed: R24.1, U20.19
unnamed: D5.A, R25.2
unnamed: L6.P$1, U23.7
unnamed: C58.1, U24.31
unnamed: C60.1, C63.1, R26.1, U24.33
unnamed: C61.1, U24.40
unnamed: R28.1, U24.18
unnamed: R29.1, U24.19
unnamed: D6.A, R30.2
P2.0: U1.1, U4.11
P2.1: U1.2, U4.10
P2.2: U1.3, U4.9
P2.3: U1.4, U4.8
P2.4: U1.5, U4.7
P2.5: U6.10, U8.2
P2.6: U6.9, U8.3
P2.7: U6.8, U8.4
P2.8: U6.7, U8.5
P2.9: U6.11, U8.1
P2.10: U10.10, U12.2
P2.11: U10.9, U12.3
P2.12: U10.8, U12.4
P2.13: U10.7, U12.5
P2.14: U10.11, U12.1
P2.15: U14.10, U16.2
P2.16: U14.9, U16.3
P2.17: U14.8, U16.4
P2.18: U14.7, U16.5
P2.19: U14.11, U16.1
P2.20: U18.10, U20.2
P2.21: U18.9, U20.3
P2.22: U18.8, U20.4
P2.23: U18.7, U20.5
P2.24: U18.11, U20.1
P2.25: U22.10, U24.2
P2.26: U22.9, U24.3
P2.27: U22.8, U24.4
P2.28: U22.7, U24.5
P2.29: U22.11, U24.1
P3.1: J15.2, TP5.P$1, U8.12
P3.2: J2.2, TP1.P$1, U1.12
P3.3: J2.4, TP2.P$1, U1.13
P3.4: J15.4, TP6.P$1, U8.13
P3.5: J24.2, TP9.P$1, U12.12
P3.6: J24.4, TP10.P$1, U12.13
P3.7: J33.2, TP13.P$1, U16.12
P3.8: J33.4, TP14.P$1, U16.13
P3.9: J42.2, TP17.P$1, U20.12
P3.10: J42.4, TP18.P$1, U20.13
P3.11: J51.2, TP21.P$1, U24.12
P3.12: J51.4, TP22.P$1, U24.13
SCL: J3.4, U1.26, U3.A8
SCL1: J13.4, U5.A8, U8.26
SCL2: J22.4, U9.A8, U12.26
SCL3: J31.4, U13.A8, U16.26
SCL4: J40.4, U17.A8, U20.26
SCL5: J49.4, U21.A8, U24.26
SDA: J3.3, U1.27, U3.A7
SDA1: J13.3, U5.A7, U8.27
SDA2: J22.3, U9.A7, U12.27
SDA3: J31.3, U13.A7, U16.27
SDA4: J40.3, U17.A7, U20.27
SDA5: J49.3, U21.A7, U24.27
SERVO_1: J16.2, U5.A15
SERVO_2: J16.1, U5.A16
SERVO_3: J25.2, U9.A15
SERVO_4: J25.1, U9.A16
SERVO_5: J34.2, U13.A15
SERVO_6: J34.1, U13.A16
SERVO_7: J43.2, U17.A15
SERVO_8: J43.1, U17.A16
SERVO_9: J52.2, U21.A15
SERVO_10: J52.1, U21.A16
SERVO_15: J9.1, U3.A16
SERVO_16: J9.2, U3.A15
SLED: R2.1, U1.14
SLED1: R10.1, U8.14
SLED2: R15.1, U12.14
SLED3: R20.1, U16.14
SLED4: R25.1, U20.14
SLED5: R30.1, U24.14
U2.1: S2.2, U8.6
U2.2: S3.2, U12.6
U2.3: S4.2, U16.6
U2.4: S5.2, U20.6
U2.5: S1.2, U1.6
U2.6: S6.2, U24.6
VCC: C3.1, C10.1, C11.1, J1.PWR, J9.3, J9.4, U2.2, U2.3, U4.1
VCC1: C12.1, C21.1, C22.1, J14.PWR, J16.3, J16.4, U6.1, U7.2, U7.3
VCC2: C23.1, C32.1, C33.1, J23.PWR, J25.3, J25.4, U10.1, U11.2, U11.3
VCC3: C34.1, C43.1, C44.1, J32.PWR, J34.3, J34.4, U14.1, U15.2, U15.3
VCC4: C45.1, C54.1, C55.1, J41.PWR, J43.3, J43.4, U18.1, U19.2, U19.3
VCC5: C56.1, C65.1, C66.1, J50.PWR, J52.3, J52.4, U22.1, U23.2, U23.3
VDDD: C1.1, C2.1, R1.1, U1.32
VDDD1: C15.1, C18.1, R7.1, U8.32
VDDD2: C26.1, C29.1, R12.1, U12.32
VDDD3: C37.1, C40.1, R17.1, U16.32
VDDD4: C48.1, C51.1, R22.1, U20.32
VDDD5: C59.1, C62.1, R27.1, U24.32

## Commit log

2017-03-30 v01 changes
    -Added 4.7k pullups to PSoC pins 4.0 and 4.1
    - Added status LED
2017-03-30 Changed name from motobit to follow naming conventions
2017-03-31 Design Review Changes
    - Added staking vias to barrel connector and motor connector
    - Added two servo connectors
    - Moved vias that were exposed for motor driver heatsink
    - Added selective solder path
    - Added mounting holes
    - Rounded corners to match micro:bit
2017-04-03 QC Fixes
    - Removed excess copper around PSoC center pad
    - Added names and values to buck converter and inductor
    - Added note about solder mask color finish
2017-04-18 Updated Changes
    Made a bunch of changes based on suggestions from education
2017-04-19 Updated Measures Layer
2017-04-20 Design review changes
2017-04-20 Fixed part number for 2 pin female header
2017-04-21 Rounded Corners
2017-05-18 V10 Changes
    - Replaced 2x3 female headers to male
    - Changed net label on heatsink mounting hole to GND
    - Increased distance between exposed pad and motor connectors
2017-05-22 Touched up traces
    A few traces had 90deg bends, replaced with 45deg bends
2017-05-25 created panel v10
2017-07-21 Updating license, adding readme
2019-01-08 Micro:bot Example Code HEX files
    Add compiled MakeCode example code used in kit.
2019-01-21 Add Wireless Remote Control with micro:bit examples
2019-09-04 v20
    -Updated silk to buzzard text
    -Updated the supply range to 11V max
    -Replaced 2.2uH inductor of buck regulator
    -Added QWIIC Connector
2019-09-04 Design Review Changes
    pushed a couple traces to get better ground pour coverage.
2019-09-04 v20 update
    Updated LED to current footprint and moved barrel connector in to reduce overhanging parts
2019-09-05 QC Fixes
    Replaced switch with short leads
2019-09-11 Update SparkFun_Micro_Bit_Moto_Bit.brd
    Moved barrel jack in a little bit more for panelization.
2019-10-07 v20_cont
    Added micro:bit SMD footprint and test points.
2019-10-09 Design review changes
    Moved test points to line up with TB pogo pins
2019-10-11 Updated card edge connector PROD_ID
2019-10-11 Update SparkFun_Micro_Bit_Moto_Bit.brd
    Removed extra labels on tPlace
2019-10-14 panel
2019-12-16 v21
    - Replaced S1 with new switch
    - Added 4.7k pull up resistors for I2C data out
2020-01-22 Fix Bugs in Examples Using Line Following Sensors
    - Update experiment 2 and 3 with improved line following examples for with option to debug via MakeCode console. Previous examples did not actually read a dark surface correctly...
    - Add some animated arrows for the user to see what button to press when the micro:bit initializes
    - Include notes for each condition statement
    - Broke up experiment 3 into two parts for users to easily digest.
    - Update battle bot example so it does not randomly "attack" based on line following readings on "collision." That's not how line following sensors work...
